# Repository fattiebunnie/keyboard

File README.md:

# Keyboard project 

This repo contains packages from different other repos so it will be easier to create a keyboard. 

## Keyboard 65 

65% keyboard

## Reference 

[tmk's keyboard_parts](https://github.com/tmk/keyboard_parts.pretty)

[tmk's kicad_lib](https://github.com/tmk/kicad_lib_tmk)

[egladman's keebs](https://github.com/egladman/keebs.pretty)

[mintexists' whiteboard](https://github.com/mintexists/WhiteBoard/tree/main)

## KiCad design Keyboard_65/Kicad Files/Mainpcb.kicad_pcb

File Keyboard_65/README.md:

# Design was taken from [WhiteBoard by mintexists](https://github.com/mintexists/WhiteBoard/tree/main)

## Keyboard form factor

This keyboard is a 65% Keyboard with a knob and place for 2 screens to go onto 

### 3D model of the keyboard parts 

#### Top Plate

#### Bot Plate

#### PCB

#### Assembly

## Tools

### Kayboard Layout Editor 

[Keyboard layout editor](https://www.keyboard-layout-editor.com/##@@=~%0A%60&=!%0A1&=%2F@%0A2&=%23%0A3&=$%0A4&=%25%0A5&=%5E%0A6&=%2F&%0A7&=*%0A8&=(%0A9&=)%0A0&=%2F_%0A-&=+%0A%2F=&_w:2%3B&=Backspace&_x:0.25%3B&=Insert&=Page%20Up%3B&@_w:1.5%3B&=Tab&=Q&=W&=E&=R&=T&=Y&=U&=I&=O&=P&=%7B%0A%5B&=%7D%0A%5D&_w:1.5%3B&=%7C%0A%5C&_x:0.25%3B&=Delete&=Page%20Down%3B&@_w:1.75%3B&=Caps%20Lock&=A&=S&=D&=F&=G&=H&=J&=K&=L&=%2F:%0A%2F%3B&=%22%0A'&_w:2.25%3B&=Enter%3B&@_w:2.25%3B&=Shift&=Z&=X&=C&=V&=B&=N&=M&=%3C%0A,&=%3E%0A.&=%3F%0A%2F%2F&_w:2.75%3B&=Shift&_x:0.25%3B&=%E2%86%91%3B&@_w:1.25%3B&=Ctrl&_w:1.25%3B&=Win&_w:1.25%3B&=Alt&_a:7&w:6.25%3B&=&_a:4&w:1.25%3B&=Alt&_w:1.25%3B&=Ctrl&_w:1.25%3B&=Menu&_x:0.5%3B&=%E2%86%90&=%E2%86%93&=%E2%86%92) is used for the holes for top plate. Though it may be unnecessary but aesthetics ig.

### Builder

[builder](http://builder.swillkb.com/) for the mounting holes. Copying the layout and adding pasting it into builder gives u the generated mounting holes.

### SVG2ShenZhen

[Badgeek's SVG to ShenZhen](https://github.com/badgeek/svg2shenzhen) makes svg into components in kicad.

### ZMK Firmware

ZMK Firmware was being used because it supported both bluetooth and I2C for display. 

# Complete build

Soldering Job: 

I soldered the pins and then snipped the excess pins off together with some solder so it is as flush as possible and does not leave excess pointy edges that will end up scratching the user (possibly just me idk) in the future.

Build:

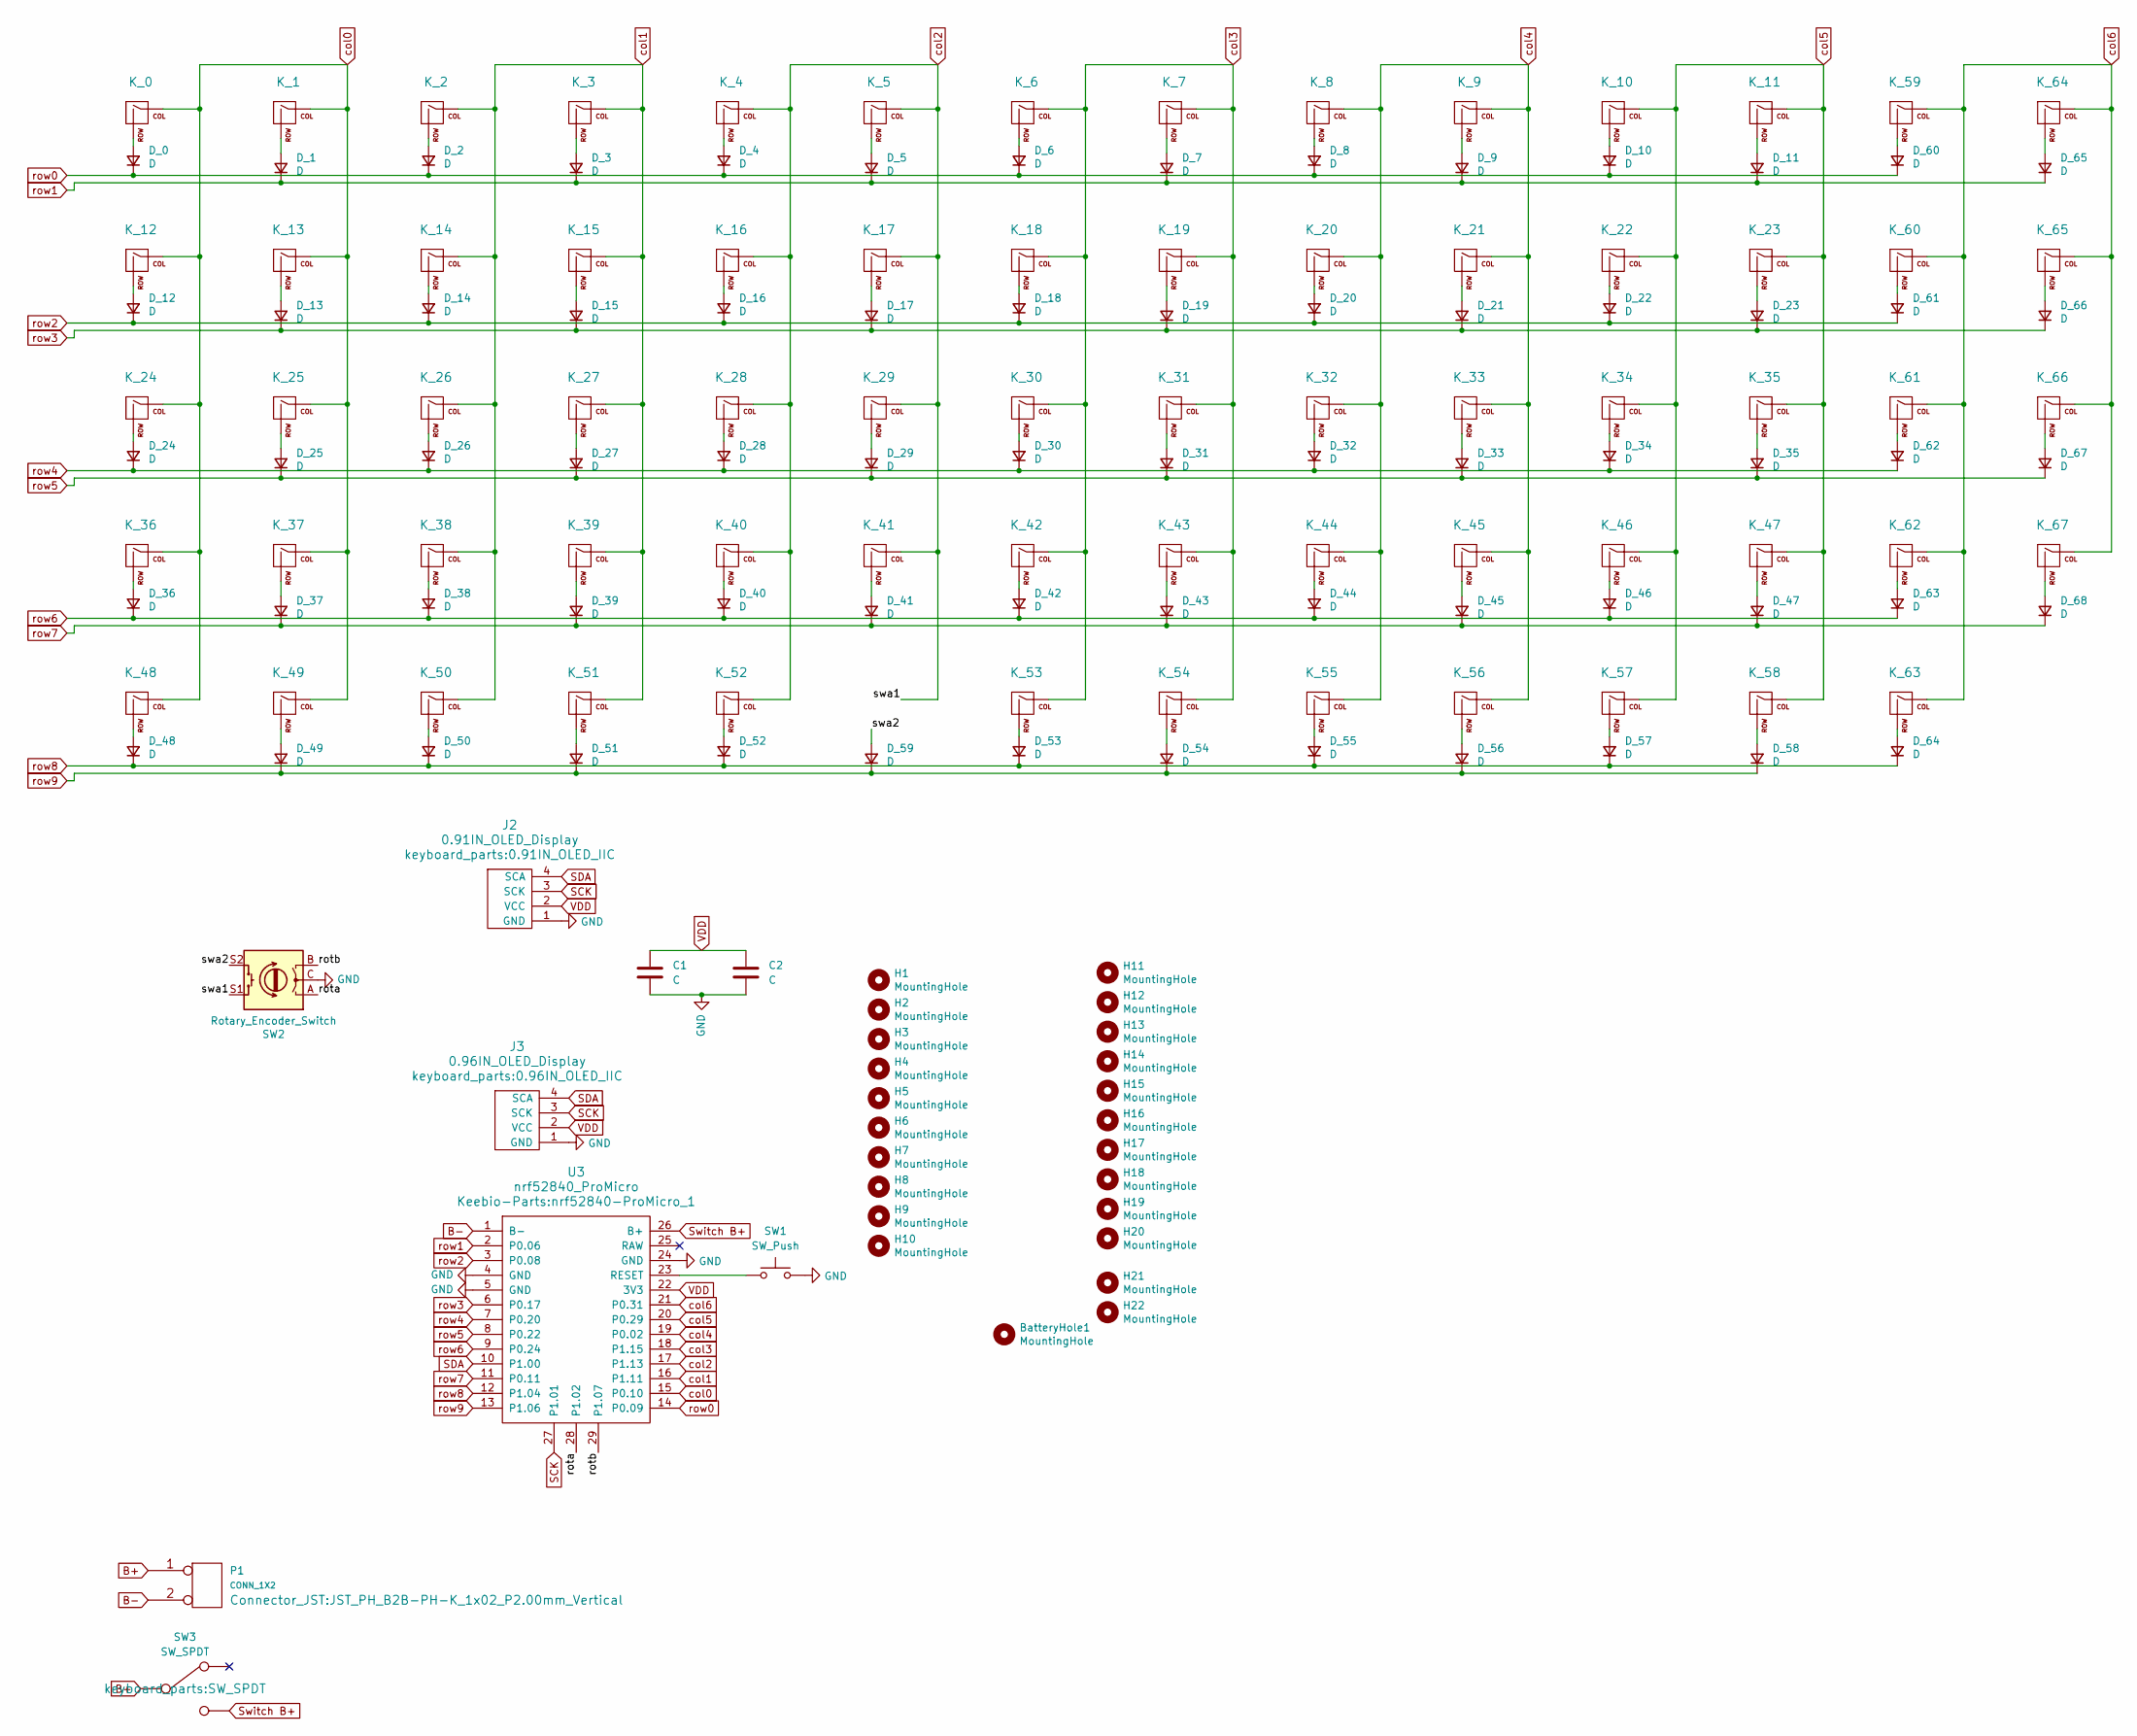
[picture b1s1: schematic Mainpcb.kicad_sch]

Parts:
BatteryHole1: MountingHole; MountingHole_5.3mm_M5
C1, C2: C; C_0805_2012Metric_Pad1.18x1.45mm_HandSolder
D_0, D_1, D_2, D_3, D_4, D_5, D_6, D_7, D_8, D_9, D_10, D_11, D_12, D_13, D_14, D_15, D_16, D_17, D_18, D_19, D_20, D_21, D_22, D_23, D_24, D_25, D_26, D_27, D_28, D_29, D_30, D_31, D_32, D_33, D_34, D_35, D_36, D_37, D_38, D_39, D_40, D_41, D_42, D_43, D_44, D_45, D_46, D_47, D_48, D_49, D_50, D_51, D_52, D_53, D_54, D_55, D_56, D_57, D_58, D_59, D_60, D_61, D_62, D_63, D_64, D_65, D_66, D_67, D_68: D; D_SOD123_axial
H1, H2, H3, H4, H5, H6, H7, H8, H9, H10, H11, H12, H13, H14, H15, H16, H17, H18, H19, H20, H21, H22: MountingHole; MountingHole_2.2mm_M2
J2: 0.91IN_OLED_Display; 0.91IN_OLED_IIC
J3: 0.96IN_OLED_Display; 0.96IN_OLED_IIC
K_0, K_1, K_2, K_3, K_4, K_5, K_6, K_7, K_8, K_9, K_10, K_11, K_12, K_13, K_14, K_15, K_16, K_17, K_18, K_19, K_20, K_21, K_22, K_23, K_24, K_25, K_26, K_27, K_28, K_29, K_30, K_31, K_32, K_33, K_34, K_35, K_36, K_37, K_38, K_39, K_40, K_41, K_42, K_43, K_44, K_45, K_46, K_47, K_48, K_49, K_50, K_51, K_52, K_53, K_54, K_55, K_56, K_57, K_58, K_59, K_60, K_61, K_62, K_63, K_64, K_65, K_66, K_67: KEYSW; Kailh_socket_MX
P1: CONN_1X2; JST_PH_B2B-PH-K_1x02_P2.00mm_Vertical
SW1: SW_Push; SW_Push_1P1T_XKB_TS-1187A
SW2: Rotary_Encoder_Switch; RotaryEncoder_Alps_EC11E-Switch_Vertical_H20mm_1
SW3: SW_SPDT
U3: nrf52840_ProMicro; nrf52840-ProMicro_1

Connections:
/rota: SW2.A, U3.28 (P1.02)
/rotb: SW2.B, U3.29 (P1.07)
/swa2: D_59.2 (A), SW2.S2
B+: P1.1, SW3.2
B-: P1.2, U3.1 (B-)
GND: C1.2, C2.2, J2.1 (GND), J3.1 (GND), SW1.2, SW2.C, U3.4 (GND), U3.5 (GND), U3.24 (GND)
unnamed: D_0.2 (A), K_0.2 (ROW)
unnamed: D_1.2 (A), K_1.2 (ROW)
unnamed: D_2.2 (A), K_2.2 (ROW)
unnamed: D_3.2 (A), K_3.2 (ROW)
unnamed: D_4.2 (A), K_4.2 (ROW)
unnamed: D_5.2 (A), K_5.2 (ROW)
unnamed: D_6.2 (A), K_6.2 (ROW)
unnamed: D_7.2 (A), K_7.2 (ROW)
unnamed: D_8.2 (A), K_8.2 (ROW)
unnamed: D_9.2 (A), K_9.2 (ROW)
unnamed: D_10.2 (A), K_10.2 (ROW)
unnamed: D_11.2 (A), K_11.2 (ROW)
unnamed: D_12.2 (A), K_12.2 (ROW)
unnamed: D_13.2 (A), K_13.2 (ROW)
unnamed: D_14.2 (A), K_14.2 (ROW)
unnamed: D_15.2 (A), K_15.2 (ROW)
unnamed: D_16.2 (A), K_16.2 (ROW)
unnamed: D_17.2 (A), K_17.2 (ROW)
unnamed: D_18.2 (A), K_18.2 (ROW)
unnamed: D_19.2 (A), K_19.2 (ROW)
unnamed: D_20.2 (A), K_20.2 (ROW)
unnamed: D_21.2 (A), K_21.2 (ROW)
unnamed: D_22.2 (A), K_22.2 (ROW)
unnamed: D_23.2 (A), K_23.2 (ROW)
unnamed: D_24.2 (A), K_24.2 (ROW)
unnamed: D_25.2 (A), K_25.2 (ROW)
unnamed: D_26.2 (A), K_26.2 (ROW)
unnamed: D_27.2 (A), K_27.2 (ROW)
unnamed: D_28.2 (A), K_28.2 (ROW)
unnamed: D_29.2 (A), K_29.2 (ROW)
unnamed: D_30.2 (A), K_30.2 (ROW)
unnamed: D_31.2 (A), K_31.2 (ROW)
unnamed: D_32.2 (A), K_32.2 (ROW)
unnamed: D_33.2 (A), K_33.2 (ROW)
unnamed: D_34.2 (A), K_34.2 (ROW)
unnamed: D_35.2 (A), K_35.2 (ROW)
unnamed: D_36.2 (A), K_36.2 (ROW)
unnamed: D_37.2 (A), K_37.2 (ROW)
unnamed: D_38.2 (A), K_38.2 (ROW)
unnamed: D_39.2 (A), K_39.2 (ROW)
unnamed: D_40.2 (A), K_40.2 (ROW)
unnamed: D_41.2 (A), K_41.2 (ROW)
unnamed: D_42.2 (A), K_42.2 (ROW)
unnamed: D_43.2 (A), K_43.2 (ROW)
unnamed: D_44.2 (A), K_44.2 (ROW)
unnamed: D_45.2 (A), K_45.2 (ROW)
unnamed: D_46.2 (A), K_46.2 (ROW)
unnamed: D_47.2 (A), K_47.2 (ROW)
unnamed: D_48.2 (A), K_48.2 (ROW)
unnamed: D_49.2 (A), K_49.2 (ROW)
unnamed: D_50.2 (A), K_50.2 (ROW)
unnamed: D_51.2 (A), K_51.2 (ROW)
unnamed: D_52.2 (A), K_52.2 (ROW)
unnamed: D_53.2 (A), K_53.2 (ROW)
unnamed: D_54.2 (A), K_54.2 (ROW)
unnamed: D_55.2 (A), K_55.2 (ROW)
unnamed: D_56.2 (A), K_56.2 (ROW)
unnamed: D_57.2 (A), K_57.2 (ROW)
unnamed: D_58.2 (A), K_58.2 (ROW)
unnamed: D_60.2 (A), K_59.2 (ROW)
unnamed: D_61.2 (A), K_60.2 (ROW)
unnamed: D_62.2 (A), K_61.2 (ROW)
unnamed: D_63.2 (A), K_62.2 (ROW)
unnamed: D_64.2 (A), K_63.2 (ROW)
unnamed: D_65.2 (A), K_64.2 (ROW)
unnamed: D_66.2 (A), K_65.2 (ROW)
unnamed: D_67.2 (A), K_66.2 (ROW)
unnamed: D_68.2 (A), K_67.2 (ROW)
unnamed: SW1.1, U3.23 (RESET)
SCK: J2.3 (SCK), J3.3 (SCK), U3.27 (P1.01)
SDA: J2.4 (SCA), J3.4 (SCA), U3.10 (P1.00)
Switch B+: SW3.3, U3.26 (B+)
VDD: C1.1, C2.1, J2.2 (VCC), J3.2 (VCC), U3.22 (3V3)
col0: K_0.1 (COL), K_1.1 (COL), K_12.1 (COL), K_13.1 (COL), K_24.1 (COL), K_25.1 (COL), K_36.1 (COL), K_37.1 (COL), K_48.1 (COL), K_49.1 (COL), U3.15 (P0.10)
col1: K_2.1 (COL), K_3.1 (COL), K_14.1 (COL), K_15.1 (COL), K_26.1 (COL), K_27.1 (COL), K_38.1 (COL), K_39.1 (COL), K_50.1 (COL), K_51.1 (COL), U3.16 (P1.11)
col2: K_4.1 (COL), K_5.1 (COL), K_16.1 (COL), K_17.1 (COL), K_28.1 (COL), K_29.1 (COL), K_40.1 (COL), K_41.1 (COL), K_52.1 (COL), SW2.S1, U3.17 (P1.13)
col3: K_6.1 (COL), K_7.1 (COL), K_18.1 (COL), K_19.1 (COL), K_30.1 (COL), K_31.1 (COL), K_42.1 (COL), K_43.1 (COL), K_53.1 (COL), K_54.1 (COL), U3.18 (P1.15)
col4: K_8.1 (COL), K_9.1 (COL), K_20.1 (COL), K_21.1 (COL), K_32.1 (COL), K_33.1 (COL), K_44.1 (COL), K_45.1 (COL), K_55.1 (COL), K_56.1 (COL), U3.19 (P0.02)
col5: K_10.1 (COL), K_11.1 (COL), K_22.1 (COL), K_23.1 (COL), K_34.1 (COL), K_35.1 (COL), K_46.1 (COL), K_47.1 (COL), K_57.1 (COL), K_58.1 (COL), U3.20 (P0.29)
col6: K_59.1 (COL), K_60.1 (COL), K_61.1 (COL), K_62.1 (COL), K_63.1 (COL), K_64.1 (COL), K_65.1 (COL), K_66.1 (COL), K_67.1 (COL), U3.21 (P0.31)
row0: D_0.1 (K), D_2.1 (K), D_4.1 (K), D_6.1 (K), D_8.1 (K), D_10.1 (K), D_60.1 (K), U3.14 (P0.09)
row1: D_1.1 (K), D_3.1 (K), D_5.1 (K), D_7.1 (K), D_9.1 (K), D_11.1 (K), D_65.1 (K), U3.2 (P0.06)
row2: D_12.1 (K), D_14.1 (K), D_16.1 (K), D_18.1 (K), D_20.1 (K), D_22.1 (K), D_61.1 (K), U3.3 (P0.08)
row3: D_13.1 (K), D_15.1 (K), D_17.1 (K), D_19.1 (K), D_21.1 (K), D_23.1 (K), D_66.1 (K), U3.6 (P0.17)
row4: D_24.1 (K), D_26.1 (K), D_28.1 (K), D_30.1 (K), D_32.1 (K), D_34.1 (K), D_62.1 (K), U3.7 (P0.20)
row5: D_25.1 (K), D_27.1 (K), D_29.1 (K), D_31.1 (K), D_33.1 (K), D_35.1 (K), D_67.1 (K), U3.8 (P0.22)
row6: D_36.1 (K), D_38.1 (K), D_40.1 (K), D_42.1 (K), D_44.1 (K), D_46.1 (K), D_63.1 (K), U3.9 (P0.24)
row7: D_37.1 (K), D_39.1 (K), D_41.1 (K), D_43.1 (K), D_45.1 (K), D_47.1 (K), D_68.1 (K), U3.11 (P0.11)
row8: D_48.1 (K), D_50.1 (K), D_52.1 (K), D_53.1 (K), D_55.1 (K), D_57.1 (K), D_64.1 (K), U3.12 (P1.04)
row9: D_49.1 (K), D_51.1 (K), D_54.1 (K), D_56.1 (K), D_58.1 (K), D_59.1 (K), U3.13 (P1.06)

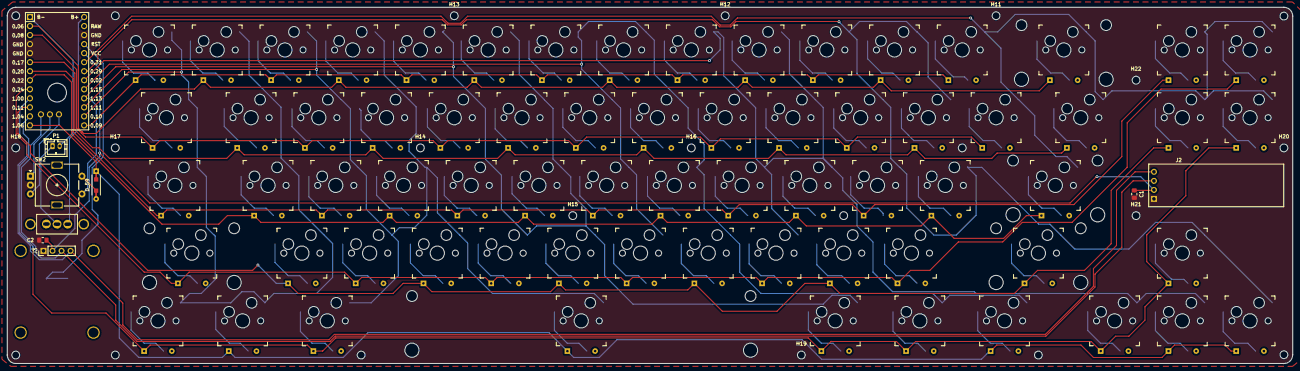
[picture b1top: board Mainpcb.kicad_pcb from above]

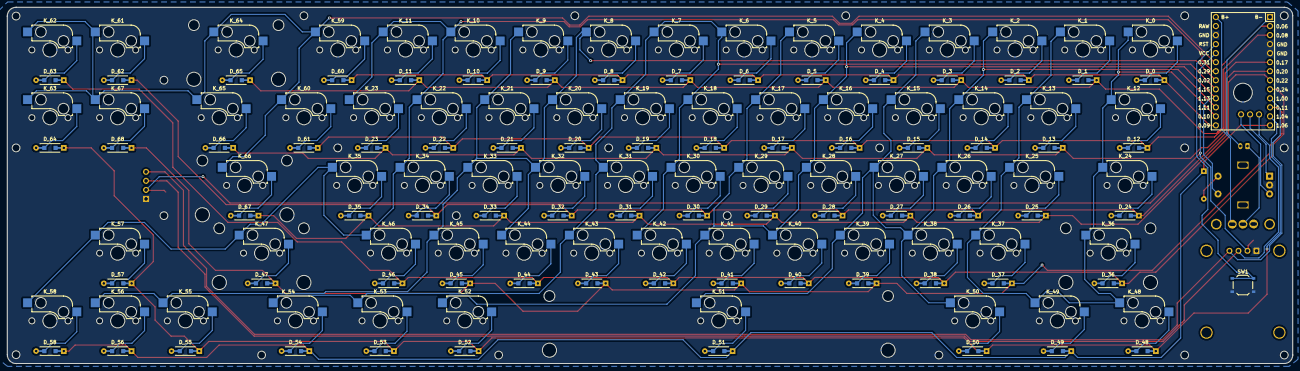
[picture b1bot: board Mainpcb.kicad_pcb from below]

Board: 2 copper layers, 361.6 x 100.2 mm, 169 parts (69 on the bottom side), 96 nets.

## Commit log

2025-01-21 added pictures of finished soldering job
2025-02-02 added final assembly
